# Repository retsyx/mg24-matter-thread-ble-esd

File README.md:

# Matter Over Thread End Sleepy Device With BLE Commissioning

Implements a motion sensor with a Silicon Labs MG24 MCU and a Bosch BMA400 IMU - be notified when the mailman delivers your mail by attaching an accelerometer to the mailbox lid. This code puts together all the bits that seem to be required for a Matter over Thread End Sleepy Device (ESD) with BLE commissioning.

## Power Consumption

Average power consumption for this setup is measured at approximately 20µA at 4V from the battery when idling.

## Requirements

* A custom PCB based on the XIAO MG24 and the BMA400 accelerometer. The design is [here](hw/board).
* A LiPo battery with a JST PH 2.0 connector.

Alternatively, you can cobble together your own setup.

## Downloading the Firmware

### Dependencies

Install OpenOCD with MG24 support to be able to flash the board.

### Download

Download the latest released [firmware](https://github.com/retsyx/mg24-matter-thread-ble-esd/releases/latest/download/MailboxMotion.zip). Unzip it.

From this project directory. Find the device serial number:

```sh
python3 scripts/find-serial.py
```

Flash the HEX file:

```sh
python3 scripts/flash.py --serial <serial> --image <path to extracted HEX file>
```

## Building

### Dependencies

* Python.
* Silicon Labs Tool (SLT), available as `slt` in PATH.
* The SLT-managed SDK and build tools at the exact versions below.
* OpenOCD with MG24 support for flashing.

Install the package versions required by [scripts/build.py](scripts/build.py):

```sh
slt install \
  simplicity-sdk/2025.6.2 \
  matter_extension/2.7.0 \
  gcc-arm-none-eabi/12.2.rel1 \
  cmake/3.30.2 \
  ninja/1.12.1 \
  zap/2026.08.24 \
  slc-cli/6.0.22 \
  java21/21.0.6 \
  python/3.10.3
```

The build script discovers installed packages through SLT.

### Build

Run from this project directory:

```sh
python3 scripts/build.py
```

The automated tests also require native host C and C++ compilers with C99 and C++17 support, such as Clang or GCC. The test driver discovers compilers in PATH; you can select them with the `CC` and `CXX` environment variables. These host compilers are separate from the firmware's ARM cross compiler. For more information, see [tests/README.txt](tests/README.txt).

To run the automated tests:

```sh
python3 scripts/test-driver.py
```

Useful build options:

```sh
python3 scripts/build.py --console
python3 scripts/build.py --battery
python3 scripts/build.py --console --battery
python3 scripts/build.py --generate
```

The default profile disables the USB UART initializer, leaves PA8/PA9 disconnected, omits the Matter shell and Thread CLI, keeps the application status LED off, and disables EM2 debugging. It also removes SWD routing and its pulls after a **five-second startup recovery window**; a later debugger connection requires the physical XIAO reset switch or a power cycle, followed by connection during that window.

* `--console` restores USB UART, the shell, Thread CLI and EM2 debugging, and keeps SWD available. UART reception holds the MCU in EM1 or a more active mode, so use this profile for diagnostics rather than battery-current comparisons.
* `--battery` enables reporting for a battery that has actually been fitted. Without it, the charger output is never interpreted as evidence of a battery.

The build produces `build/MailboxMotion` (ELF), `build/MailboxMotion.hex`, `build/MailboxMotion.bin`, and a linker map.

Silicon Labs platform files are generated from [MailboxMotion.slcp](MailboxMotion.slcp) and the maintained `config/` inputs using Studio's bundled SLC. The Matter data model is generated from [mailbox-motion.zap](config/common/mailbox-motion.zap) with ZAP.

## Flashing and Monitoring

If the running default image has already released SWD, press the **physical XIAO reset switch** or power-cycle the board immediately before starting the upload, so the debugger connects within five seconds. Automatic hardware reset through the USB bridge was tested and did not reset this target; the uploader does not provide automatic connect-under-reset recovery. Once installed, an image installed with the `--console` option keeps SWD available.

Find the CMSIS-DAP serial number for attached devices on macOS or Linux:

```sh
python3 scripts/find-serial.py
```

Check that all required tools are available for flashing:

```sh
python3 scripts/flash.py --check-tools
```

Flash using the CMSIS-DAP serial that was found earlier:

```sh
python3 scripts/flash.py --serial <serial>
```

Optionally monitor the device.

On MacOS:

```sh
python3 scripts/monitor.py --port /dev/cu.usbmodem<serial>
```

On Linux:

```sh
python3 scripts/monitor.py --port /dev/serial/by-id/*<serial>*
```

## Matter Commissioning

An uncommissioned device opens a **15-minute commissioning window at boot**. With a console build, `mailbox commission` also reopens it for 15 minutes. The command preserves active BLE pairing sessions and refuses to reopen a device that already has a Matter fabric. Resetting the MCU preserves its fabric and does not factory-reset the accessory.

With your favorite Matter commissioner (HomeKit, etc.) add the accessory.

The QR code below is for an unprovisioned device using this project's development commissioning defaults.

Commissioning values use the defaults in [CHIPProjectConfig.h](include/CHIPProjectConfig.h):

| Setting | Value |
| --- | --- |
| Manual pairing code | `34970112332` |
| Setup passcode | `20202021` |
| Long discriminator | `3840` / `0xF00` |
| Vendor ID | `0xFFF1` |
| Product ID | `0x8004` |

The test commissioning credentials are fallbacks. Provisioned commissioning data in nonvolatile memory takes precedence over those defaults, and firmware configuration changes can also change the pairing payload. Resetting the MCU preserves stored commissioning data. If credentials have been provisioned or changed, use the device's actual QR or manual pairing code. A `--console` build prints the current manual pairing code for an uncommissioned device at boot and after a successful `mailbox commission` request.

## Details

### Serial Diagnostics

With `--console`, the application uses the XIAO's USB serial bridge at **115200 baud, 8 data bits, no parity, one stop bit**. The application UART is EUSART0 on PA8/PA9. The default profile leaves those pins disconnected and supplies no UART shell or output.

At the Matter shell prompt:

```text
mailbox status
mailbox motion
mailbox battery
mailbox commission
```

* `status` prints sensor availability, occupancy, motion and fabric counts, INT1 level, dropped GPIO interrupts, battery configuration, and BLE/commissioning state.
* `motion` injects one test indication through the application queue and five-second timer. It verifies the application path without a connected accelerometer.
* `battery` requests an immediate battery attribute update; values remain unknown in the default build.
* `commission` queues a request to reopen commissioning on an uncommissioned device.

### Antenna Selection

Before starting BLE or Thread, [main.cpp](src/main.cpp) drives **PB5 high** to power the RF switch and **PB4 low** to select the onboard antenna. See Seeed's [antenna-selection instructions](https://wiki.seeedstudio.com/xiao_mg24_bluetooth/#switching-between-built-in-and-external-antennas). The application also switches off the optional Sense IMU supply on PD5 and microphone enable on PC8, keeps the battery divider off until sampling, and sends the unused onboard Puya flash a deep-power-down command. The RF switch remains powered for radio operation.

### Battery Measurement

The XIAO MG24 has an onboard switched battery divider. **PD3 enables it; PD4 measures its midpoint.** The schematic specifies equal 10 kΩ resistors, so VBAT is twice the sensed voltage. [BatteryMonitor.cpp](src/BatteryMonitor.cpp) enables the path, allows it to settle, samples IADC0 using the internal reference, and disables the path afterwards. See the [power circuit in the Seeed schematic](https://files.seeedstudio.com/wiki/XIAO_MG24/Getting_Start/XIAO_MG24_SCH.pdf).

Enable reporting with `python3 scripts/build.py --battery` only when a rechargeable battery is fitted. A voltage at VBAT does not prove that a cell is attached: USB powers the charger circuit. The default reports unknown voltage and percentage with battery presence false.

The estimate maps 3.5 V to 0% and 4.2 V to 100%, with low-battery indication below 20%.

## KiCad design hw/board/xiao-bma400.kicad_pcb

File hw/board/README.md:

# XIAO MG24 and BMA400 PCB

## BOM

| References | Manufacturer / part | Datasheet |
| --- | --- | --- |
| U1 | Seeed Studio **102010590** | [Module schematic](datasheets/seeed-xiao-mg24-schematic.pdf) |
| U2 | Bosch Sensortec **BMA400** | [BMA400](datasheets/bosch-bma400.pdf) |
| J1 | JST **S2B-PH-K-S(LF)(SN)** | [PH series](datasheets/jst-ph.pdf) |
| R1, R2 | Panasonic **ERJ-3EKF1002V** | [ERJ series](datasheets/panasonic-erj-thick-film.pdf) |
| C1, C2 | KEMET **C0603C104K5RACTU** | [X7R series](datasheets/kemet-x7r-smd.pdf) |
| C3 | KEMET **C0603C105K4RACTU** | | [X7R series](datasheets/kemet-x7r-smd.pdf) |

Order the [standard XIAO MG24](https://www.seeedstudio.com/Seeed-Studio-XIAO-MG24-p-6247.html), without fitted pin headers.

## PCB Files and Editing

The PCB is two-layer, 1.6 mm FR4.

After editing, run the installed KiCad validation/export helper from the repository root:

```sh
python3 hw/board/scripts/export.py
python3 hw/board/scripts/render.py
```

Source generators overwrite their targets:

* `generate_schematic.py` rebuilds the schematic and local symbol library
* `generate_bom.py` rebuilds both BOM copies.
* `generate_board.py` requires KiCad's existing `pcbnew` Python module and the XML netlist. Preserve manual layout changes before generating a PCB.
*  Property-only updates can use `sync_board_properties.py` to preserve the layout.

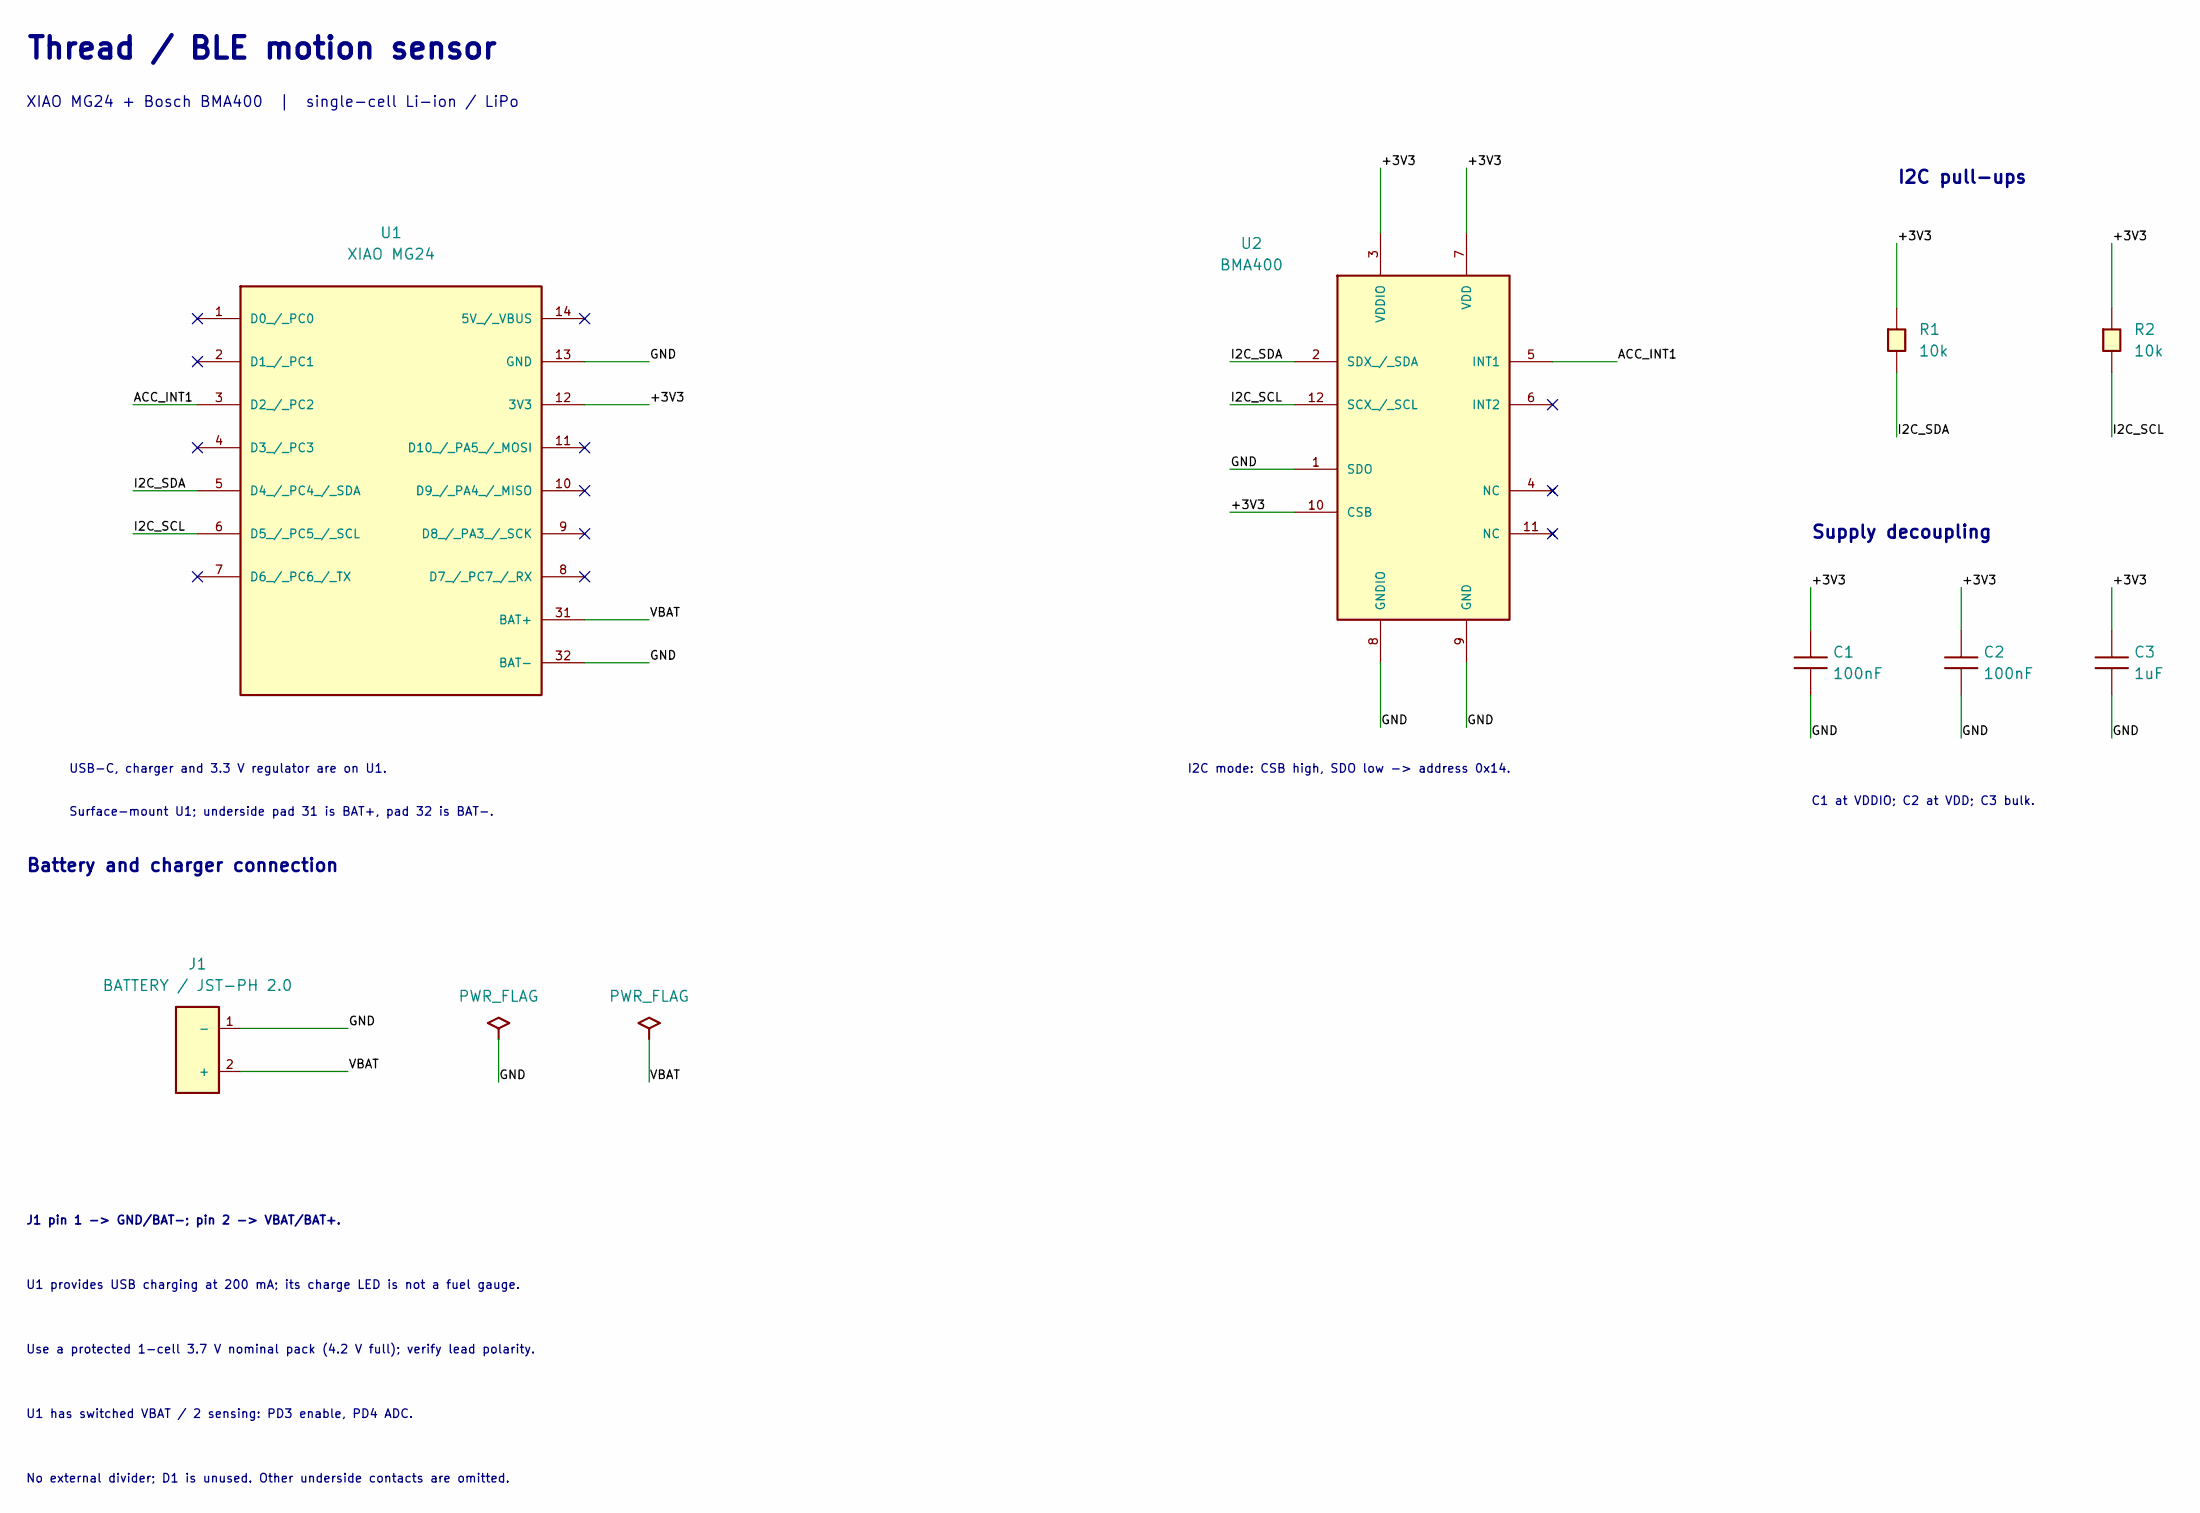
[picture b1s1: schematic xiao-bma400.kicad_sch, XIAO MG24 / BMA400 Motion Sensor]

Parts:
C1, C2: 100nF; C_0603_1608Metric; Tolerance 10%; Voltage 50V; MPN C0603C104K5RACTU
C3: 1uF; C_0603_1608Metric; Tolerance 10%; Voltage 16V; MPN C0603C105K4RACTU
J1: BATTERY / JST-PH 2.0; JST_PH_S2B-PH-K_1x02_P2.00mm_Horizontal; MPN S2B-PH-K-S(LF)(SN)
R1, R2: 10k; R_0603_1608Metric; Tolerance 1%; MPN ERJ-3EKF1002V
U1: XIAO MG24; XIAO_MG24_SMD; MPN 102010590
U2: BMA400; LGA-12_2x2mm_P0.5mm; MPN BMA400

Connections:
/+3V3: C1.1, C2.1, C3.1, R1.1, R2.1, U1.12 (3V3), U2.3 (VDDIO), U2.7 (VDD), U2.10 (CSB)
/ACC_INT1: U1.3 (D2_/_PC2), U2.5 (INT1)
/GND: C1.2, C2.2, C3.2, J1.1 (-), U1.13 (GND), U1.32 (BAT-), U2.1 (SDO), U2.8 (GNDIO), U2.9 (GND)
/I2C_SCL: R2.2, U1.6 (D5_/_PC5_/_SCL), U2.12 (SCX_/_SCL)
/I2C_SDA: R1.2, U1.5 (D4_/_PC4_/_SDA), U2.2 (SDX_/_SDA)
/VBAT: J1.2 (+), U1.31 (BAT+)

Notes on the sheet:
U1 has switched VBAT / 2 sensing: PD3 enable, PD4 ADC.
C1 at VDDIO; C2 at VDD; C3 bulk.
Battery and charger connection
I2C mode: CSB high, SDO low -> address 0x14.
Use a protected 1-cell 3.7 V nominal pack (4.2 V full); verify lead polarity.
USB-C, charger and 3.3 V regulator are on U1.
J1 pin 1 -> GND/BAT-; pin 2 -> VBAT/BAT+.
XIAO MG24 + Bosch BMA400 | single-cell Li-ion / LiPo
Surface-mount U1; underside pad 31 is BAT+, pad 32 is BAT-.
No external divider; D1 is unused. Other underside contacts are omitted.
Thread / BLE motion sensor
U1 provides USB charging at 200 mA; its charge LED is not a fuel gauge.
Supply decoupling
I2C pull-ups

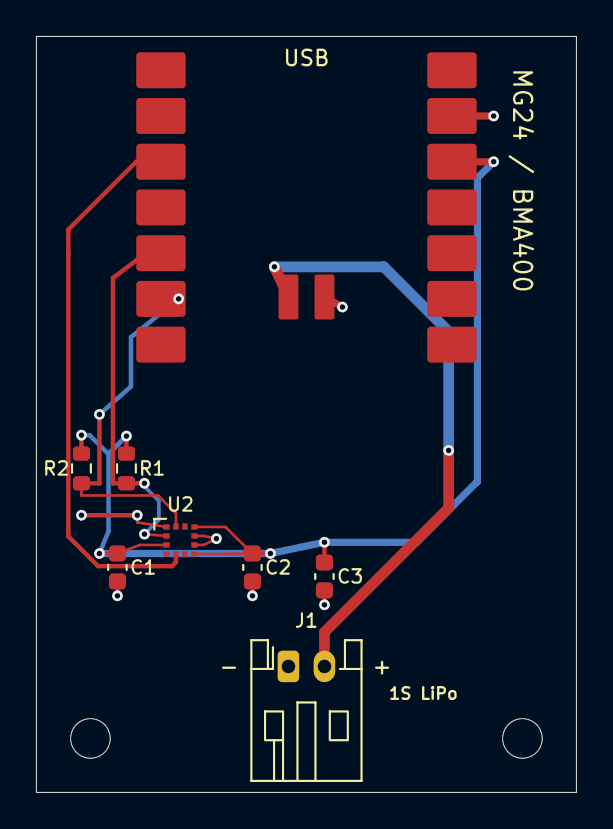
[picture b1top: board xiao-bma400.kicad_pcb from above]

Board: 2 copper layers, 30.0 x 42.0 mm, 10 parts (0 on the bottom side), 6 nets.

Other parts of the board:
H1, H2: MountingHole_2.2mm_M2
